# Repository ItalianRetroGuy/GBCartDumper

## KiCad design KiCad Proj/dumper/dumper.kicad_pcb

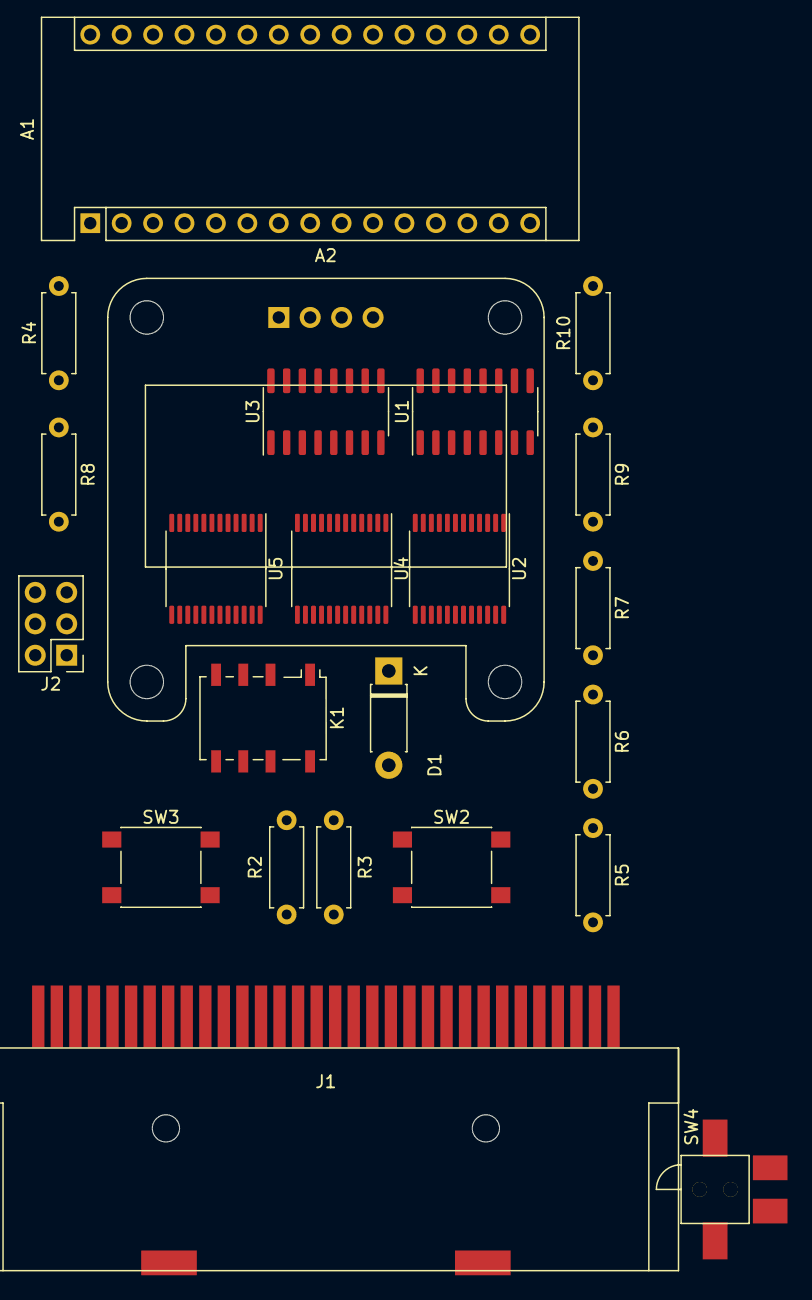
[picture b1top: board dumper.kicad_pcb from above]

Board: 2 copper layers, 23 parts (0 on the bottom side), 67 nets, no tracks yet.

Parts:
A1: Arduino_Nano_v3.x; Arduino_Nano
A2: SSD1306; Adafruit_SSD1306_I2C_Only
D1: 1N4004; D_DO-41_SOD81_P7.62mm_Horizontal
J1: CartBus; DSL_Cartridge_Reader
J2: LINK PORT; PinHeader_2x03_P2.54mm_Vertical
K1: G6K-2; Relay_DPDT_Omron_G6K-2F-Y
R2, R3, R4, R5, R6, R7, R8, R9, R10: 10K; R_Axial_DIN0207_L6.3mm_D2.5mm_P7.62mm_Horizontal
SW2, SW3: SW_SPST; SW_Push_1P1T_NO_6x6mm_H9.5mm
SW4: KFC-C-15A
U1, U3: 74HC595; SOP-16_3.9x9.9mm_P1.27mm
U2, U4, U5: SN74LVC8T245PWR; TSSOP-24_6.1x7.8mm_P0.65mm

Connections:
+3V3: A1.17, A2.2, J2.1, K1.4, K1.7, R4.2, SW2.1, SW3.1, SW4.1, U1.10, U1.16, U2.1, U2.2, U3.10, U3.16, U4.1, U4.2, U5.1
+5V: A1.27, K1.5, U2.23, U2.24, U4.23, U4.24, U5.23, U5.24
/Cart Detection/CART_VCC: J1.1, K1.6, R8.1
/Cart Detection/GB_CART_H: A1.14, J2.2, K1.3, R9.2
/Cartridge Slot/A0: J1.6, U2.14
/Cartridge Slot/A1: J1.7, U2.15
/Cartridge Slot/A2: J1.8, U2.16
/Cartridge Slot/A3: J1.9, U2.17
/Cartridge Slot/A4: J1.10, U2.18
/Cartridge Slot/A5: J1.11, U2.19
/Cartridge Slot/A6: J1.12, U2.20
/Cartridge Slot/A7: J1.13, U2.21
/Cartridge Slot/A8: J1.14, U4.14
/Cartridge Slot/A9: J1.15, U4.15
/Cartridge Slot/A10: J1.16, U4.16
/Cartridge Slot/A11: J1.17, U4.17
/Cartridge Slot/A12: J1.18, U4.18
/Cartridge Slot/A13: J1.19, U4.19
/Cartridge Slot/A14: J1.20, U4.20
/Cartridge Slot/A15: J1.21, U4.21
/Cartridge Slot/CART_CS: A1.13, J1.5, J2.4, R7.2
/Cartridge Slot/CART_RD: A1.26, J1.4, R6.2
/Cartridge Slot/CART_WR: A1.25, J1.3, R5.2
/Cartridge Slot/TD0: J1.22, U5.21
/Cartridge Slot/TD1: J1.23, U5.20
/Cartridge Slot/TD2: J1.24, U5.19
/Cartridge Slot/TD3: J1.25, U5.18
/Cartridge Slot/TD4: J1.26, U5.17
/Cartridge Slot/TD5: J1.27, U5.16
/Cartridge Slot/TD6: J1.28, U5.15
/Cartridge Slot/TD7: J1.29, U5.14
/Controller/ADDRESS_CLK: A1.6, U1.11, U3.11
/Controller/ADDRESS_DATA: A1.5, U1.14
/Controller/ADDRESS_LATCH: A1.7, U1.12, U3.12
/Controller/D0: A1.12, U5.3
/Controller/D1: A1.11, U5.4
/Controller/D2: A1.10, U5.5
/Controller/D3: A1.9, U5.6
/Controller/D4: A1.19, U5.7
/Controller/D5: A1.20, U5.8
/Controller/D6: A1.21, U5.9
/Controller/D7: A1.22, U5.10
/Controller/MISO: A1.15, J2.3, R2.2, SW2.2
/Controller/SCK: A1.16, J2.5, R3.1, SW3.2
/Controller/SCL: A1.24, A2.3
/Controller/SDA: A1.23, A2.4
/Controller/SWITCH_TRANSCEIVER: A1.8, R10.2, U5.2
GND: A1.4, A1.29, A2.1, D1.2, J1.32, J2.6, K1.8, R2.1, R3.2, R4.1, R5.1, R6.1, R7.1, R9.1, R10.1, U1.13, U2.11, U2.12, U2.13, U2.22, U3.13, U4.11, U4.12, U4.13, U4.22, U5.11, U5.12, U5.13, U5.22
unnamed: D1.1, K1.1, SW4.2
unnamed: J1.30, R8.2
unnamed: U1.1, U2.4
unnamed: U1.2, U2.5
unnamed: U1.3, U2.6
unnamed: U1.4, U2.7
unnamed: U1.5, U2.8
unnamed: U1.6, U2.9
unnamed: U1.7, U2.10
unnamed: U1.9, U3.14
unnamed: U1.15, U2.3
unnamed: U3.1, U4.4
unnamed: U3.2, U4.5
unnamed: U3.3, U4.6
unnamed: U3.4, U4.7
unnamed: U3.5, U4.8
unnamed: U3.6, U4.9
unnamed: U3.7, U4.10
unnamed: U3.15, U4.3

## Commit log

2021-08-10 Initial files
2021-08-14 Finalized schematic and PCB
2021-08-14 Moved files
2021-08-14 Re-routed doozy trace
2021-08-14 Can't remember
2021-08-17 Fixed up the schematic and PCB for two very severe omissions
    I forgot to translate the WR, RD, and CS pins and added a transceiver for those
    I also forgot that the transceivers should have CART_VCC on VccB
